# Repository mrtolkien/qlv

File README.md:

# qlv

Quelle Vie (QLV) keyboard

```plaintext
     C0  C1  C2  C3  C4    C4  C3  C2  C1  C0
R0   .   .   .   .   .     .   .   .   .   .   R4
R1   .   .   .   .   .     .   .   .   .   .   R5
R2   .   .   .   .   .     .   .   .   .   .   R6

R3            .  .   .     .   .   .           R7
```

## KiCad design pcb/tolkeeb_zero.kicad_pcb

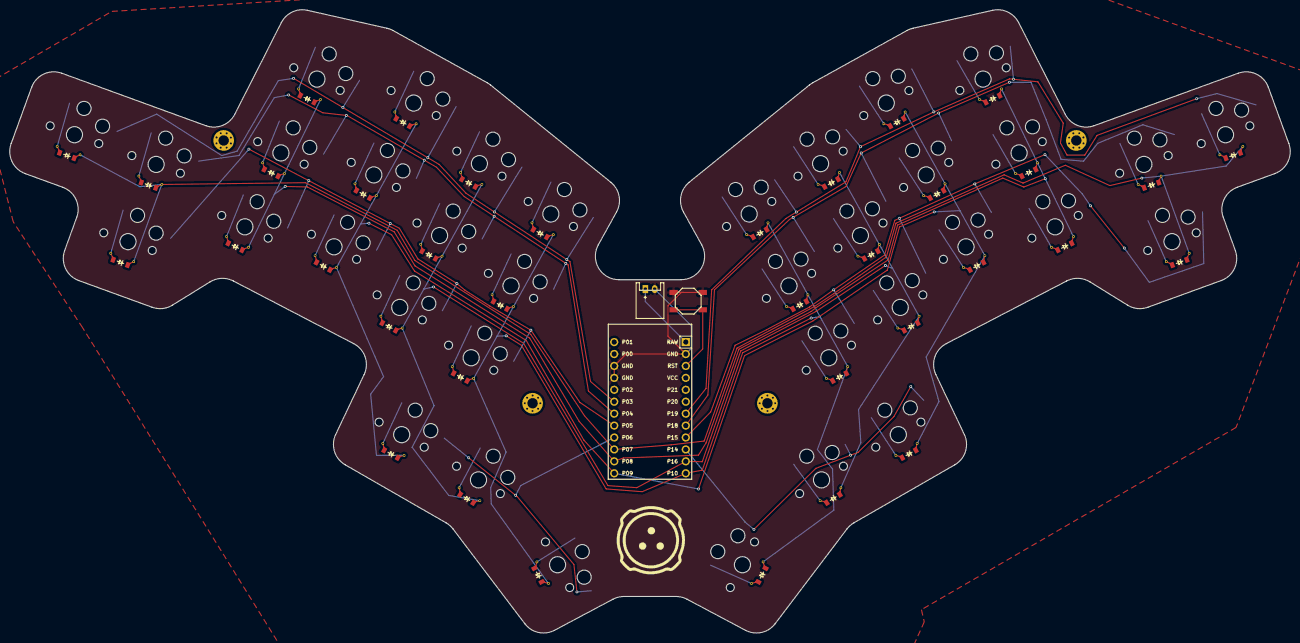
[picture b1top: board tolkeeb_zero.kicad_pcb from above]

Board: 4 copper layers, 272.7 x 132.7 mm, 115 parts (0 on the bottom side), 52 nets.

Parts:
B1: SW_TACT_ALPS_SKQGABE010
D1, D2, D3, D4, D5, D6, D7, D8, D9, D10, D11, D12, D13, D14, D15, D16, D17, D18, D19, D20, D21, D22, D23, D24, D25, D26, D27, D28, D29, D30, D31, D32, D33, D34, D35, D36: ComboDiode
JST1: JST_PH_S2B-PH-K_02x2.00mm_Angled
MCU1: ProMicro
S1, S2, S3, S4, S5, S6, S7, S8, S9, S10, S11, S12, S13, S14, S15, S16, S17, S18, S19, S20, S21, S22, S23, S24, S25, S26, S27, S28, S29, S30, S31, S32, S33, S34, S35, S36: PG1350
SB1, SB2, SB3, SB4, SB5, SB6, SB7, SB8, SB9, SB10, SB11, SB12, SB13, SB14, SB15, SB16, SB17, SB18, SB19, SB20, SB21, SB22, SB23, SB24, SB25, SB26, SB27, SB28, SB29, SB30, SB31, SB32, SB33, SB34, SB35, SB36: ChocBonusGoodies
_1, _2, _3, _4: MountingHole_2.2mm_M2_Pad_Via

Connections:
GND: B1.1, JST1.2, MCU1.2, MCU1.15, MCU1.16
P3: MCU1.18, S1.2, S6.2, S9.2, S12.2, S15.2
P4: MCU1.19, S3.2, S5.2, S8.2, S11.2, S14.2
P5: MCU1.20, S2.2, S4.2, S7.2, S10.2, S13.2
P6: MCU1.21, S31.2, S32.2, S33.2
P7: D1.1, D1.3, D1.4, D2.1, D2.3, D2.4, D3.1, D3.3, D3.4, D16.1, D16.3, D16.4, D17.1, D17.3, D17.4, D18.1, D18.3, D18.4, MCU1.22
P8: D4.1, D4.3, D4.4, D5.1, D5.3, D5.4, D6.1, D6.3, D6.4, D19.1, D19.3, D19.4, D20.1, D20.3, D20.4, D21.1, D21.3, D21.4, MCU1.23
P9: D7.1, D7.3, D7.4, D8.1, D8.3, D8.4, D9.1, D9.3, D9.4, D22.1, D22.3, D22.4, D23.1, D23.3, D23.4, D24.1, D24.3, D24.4, D31.1, D31.3, D31.4, D34.1, D34.3, D34.4, MCU1.24
P10: D13.1, D13.3, D13.4, D14.1, D14.3, D14.4, D15.1, D15.3, D15.4, D28.1, D28.3, D28.4, D29.1, D29.3, D29.4, D30.1, D30.3, D30.4, D33.1, D33.3, D33.4, D36.1, D36.3, D36.4, MCU1.12
P14: MCU1.10, S34.2, S35.2, S36.2
P15: MCU1.9, S17.2, S19.2, S22.2, S25.2, S28.2
P16: D10.1, D10.3, D10.4, D11.1, D11.3, D11.4, D12.1, D12.3, D12.4, D25.1, D25.3, D25.4, D26.1, D26.3, D26.4, D27.1, D27.3, D27.4, D32.1, D32.3, D32.4, D35.1, D35.3, D35.4, MCU1.11
P18: MCU1.8, S18.2, S20.2, S23.2, S26.2, S29.2
P19: MCU1.7, S16.2, S21.2, S24.2, S27.2, S30.2
RAW: JST1.1, MCU1.1
RST: B1.2, MCU1.3
center_default: D32.2, D32.6, D32.7, S32.1
index_bottom: D10.2, D10.6, D10.7, S10.1
index_home: D11.2, D11.6, D11.7, S11.1
index_top: D12.2, D12.6, D12.7, S12.1
inner_bottom: D13.2, D13.6, D13.7, S13.1
inner_default: D31.2, D31.6, D31.7, S31.1
inner_home: D14.2, D14.6, D14.7, S14.1
inner_top: D15.2, D15.6, D15.7, S15.1
middle_bottom: D7.2, D7.6, D7.7, S7.1
middle_home: D8.2, D8.6, D8.7, S8.1
middle_top: D9.2, D9.6, D9.7, S9.1
mirror_center_default: D35.2, D35.6, D35.7, S35.1
mirror_index_bottom: D25.2, D25.6, D25.7, S25.1
mirror_index_home: D26.2, D26.6, D26.7, S26.1
mirror_index_top: D27.2, D27.6, D27.7, S27.1
mirror_inner_bottom: D28.2, D28.6, D28.7, S28.1
mirror_inner_default: D34.2, D34.6, D34.7, S34.1
mirror_inner_home: D29.2, D29.6, D29.7, S29.1
mirror_inner_top: D30.2, D30.6, D30.7, S30.1
mirror_middle_bottom: D22.2, D22.6, D22.7, S22.1
mirror_middle_home: D23.2, D23.6, D23.7, S23.1
mirror_middle_top: D24.2, D24.6, D24.7, S24.1
mirror_outer_default: D36.2, D36.6, D36.7, S36.1
mirror_pinky_bottom: D17.2, D17.6, D17.7, S17.1
mirror_pinky_extension_home: D16.2, D16.6, D16.7, S16.1
mirror_pinky_home: D18.2, D18.6, D18.7, S18.1
mirror_ring_bottom: D19.2, D19.6, D19.7, S19.1
mirror_ring_home: D20.2, D20.6, D20.7, S20.1
mirror_ring_top: D21.2, D21.6, D21.7, S21.1
outer_default: D33.2, D33.6, D33.7, S33.1
pinky_bottom: D2.2, D2.6, D2.7, S2.1
pinky_extension_home: D1.2, D1.6, D1.7, S1.1
pinky_home: D3.2, D3.6, D3.7, S3.1
ring_bottom: D4.2, D4.6, D4.7, S4.1
ring_home: D5.2, D5.6, D5.7, S5.1
ring_top: D6.2, D6.6, D6.7, S6.1

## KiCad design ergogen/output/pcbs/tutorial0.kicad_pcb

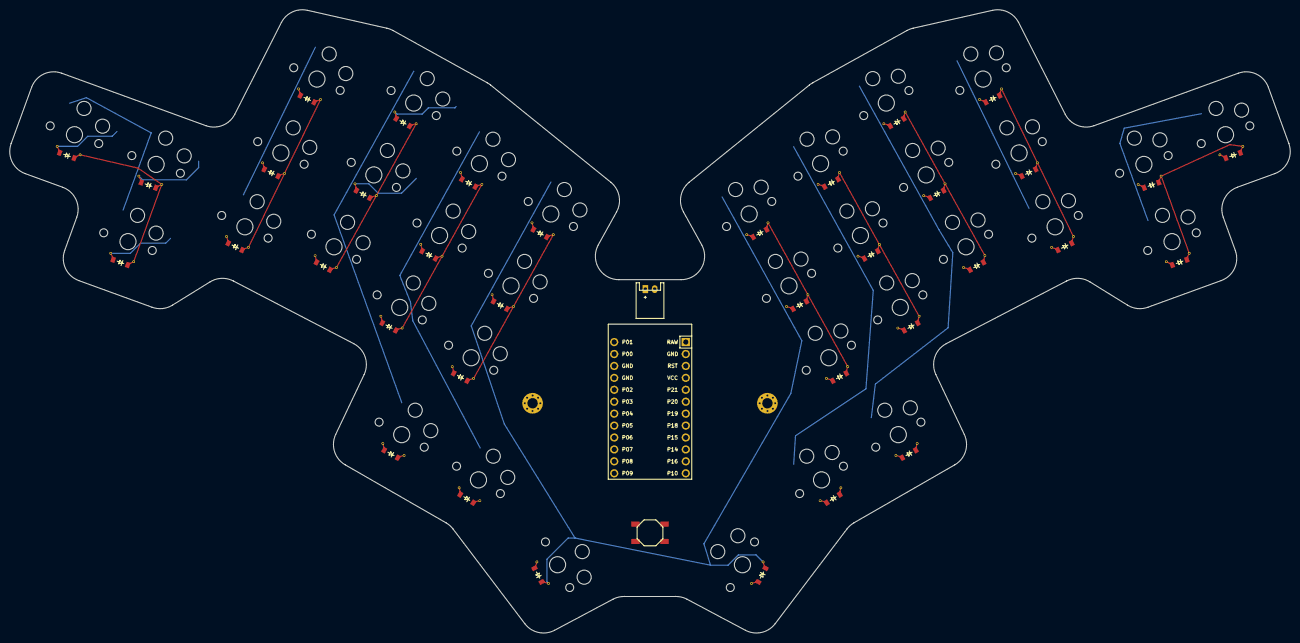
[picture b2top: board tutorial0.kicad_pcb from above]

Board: 2 copper layers, 272.7 x 132.7 mm, 77 parts (0 on the bottom side), 44 nets.

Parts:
B1: SW_TACT_ALPS_SKQGABE010
D1, D2, D3, D4, D5, D6, D7, D8, D9, D10, D11, D12, D13, D14, D15, D16, D17, D18, D19, D20, D21, D22, D23, D24, D25, D26, D27, D28, D29, D30, D31, D32, D33, D34, D35, D36: ComboDiode
JST1: JST_PH_S2B-PH-K_02x2.00mm_Angled
MCU1: ProMicro
S1, S2, S3, S4, S5, S6, S7, S8, S9, S10, S11, S12, S13, S14, S15, S16, S17, S18, S19, S20, S21, S22, S23, S24, S25, S26, S27, S28, S29, S30, S31, S32, S33, S34, S35, S36: PG1350
_1, _2: MountingHole_2.2mm_M2_Pad_Via

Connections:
GND: B1.1, JST1.2, MCU1.2, MCU1.15, MCU1.16
P7: D1.1, D1.3, D1.4, D2.1, D2.3, D2.4, D3.1, D3.3, D3.4, D16.1, D16.3, D16.4, D17.1, D17.3, D17.4, D18.1, D18.3, D18.4, MCU1.22, S1.1, S2.1, S3.1, S16.1, S17.1, S18.1
P8: D4.1, D4.3, D4.4, D5.1, D5.3, D5.4, D6.1, D6.3, D6.4, D19.1, D19.3, D19.4, D20.1, D20.3, D20.4, D21.1, D21.3, D21.4, MCU1.23, S4.1, S5.1, S6.1, S19.1, S20.1, S21.1
P9: D7.1, D7.3, D7.4, D8.1, D8.3, D8.4, D9.1, D9.3, D9.4, D22.1, D22.3, D22.4, D23.1, D23.3, D23.4, D24.1, D24.3, D24.4, D31.1, D31.3, D31.4, D34.1, D34.3, D34.4, MCU1.24, S7.1, S8.1, S9.1, S22.1, S23.1, S24.1, S31.1, S34.1
P10: D13.1, D13.3, D13.4, D14.1, D14.3, D14.4, D15.1, D15.3, D15.4, D28.1, D28.3, D28.4, D29.1, D29.3, D29.4, D30.1, D30.3, D30.4, D33.1, D33.3, D33.4, D36.1, D36.3, D36.4, MCU1.12, S13.1, S14.1, S15.1, S28.1, S29.1, S30.1, S33.1, S36.1
P16: D10.1, D10.3, D10.4, D11.1, D11.3, D11.4, D12.1, D12.3, D12.4, D25.1, D25.3, D25.4, D26.1, D26.3, D26.4, D27.1, D27.3, D27.4, D32.1, D32.3, D32.4, D35.1, D35.3, D35.4, MCU1.11, S10.1, S11.1, S12.1, S25.1, S26.1, S27.1, S32.1, S35.1
RAW: JST1.1, MCU1.1
RST: B1.2, MCU1.3
center_default: D32.2, D32.6, D32.7, S32.2
index_bottom: D10.2, D10.6, D10.7, S10.2
index_home: D11.2, D11.6, D11.7, S11.2
index_top: D12.2, D12.6, D12.7, S12.2
inner_bottom: D13.2, D13.6, D13.7, S13.2
inner_default: D31.2, D31.6, D31.7, S31.2
inner_home: D14.2, D14.6, D14.7, S14.2
inner_top: D15.2, D15.6, D15.7, S15.2
middle_bottom: D7.2, D7.6, D7.7, S7.2
middle_home: D8.2, D8.6, D8.7, S8.2
middle_top: D9.2, D9.6, D9.7, S9.2
mirror_center_default: D35.2, D35.6, D35.7, S35.2
mirror_index_bottom: D25.2, D25.6, D25.7, S25.2
mirror_index_home: D26.2, D26.6, D26.7, S26.2
mirror_index_top: D27.2, D27.6, D27.7, S27.2
mirror_inner_bottom: D28.2, D28.6, D28.7, S28.2
mirror_inner_default: D34.2, D34.6, D34.7, S34.2
mirror_inner_home: D29.2, D29.6, D29.7, S29.2
mirror_inner_top: D30.2, D30.6, D30.7, S30.2
mirror_middle_bottom: D22.2, D22.6, D22.7, S22.2
mirror_middle_home: D23.2, D23.6, D23.7, S23.2
mirror_middle_top: D24.2, D24.6, D24.7, S24.2
mirror_outer_default: D36.2, D36.6, D36.7, S36.2
mirror_pinky_bottom: D17.2, D17.6, D17.7, S17.2
mirror_pinky_extension_home: D16.2, D16.6, D16.7, S16.2
mirror_pinky_home: D18.2, D18.6, D18.7, S18.2
mirror_ring_bottom: D19.2, D19.6, D19.7, S19.2
mirror_ring_home: D20.2, D20.6, D20.7, S20.2
mirror_ring_top: D21.2, D21.6, D21.7, S21.2
outer_default: D33.2, D33.6, D33.7, S33.2
pinky_bottom: D2.2, D2.6, D2.7, S2.2
pinky_extension_home: D1.2, D1.6, D1.7, S1.2
pinky_home: D3.2, D3.6, D3.7, S3.2
ring_bottom: D4.2, D4.6, D4.7, S4.2
ring_home: D5.2, D5.6, D5.7, S5.2
ring_top: D6.2, D6.6, D6.7, S6.2

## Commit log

2024-05-31 feat: add first pass on keyboard with custom outline
2024-05-31 feat: add row and column nets
2024-05-31 fix: make thumbs PCB a bit bigger for simpler routing
2024-05-31 feat: add runonsave configuration for the repo, generating svgs for all outlines
2024-06-06 feat: alpha4, proper scale
2024-06-06 feat: alpha 5, thumb update
2024-06-16 feat: alpha 7, keys position final
2024-06-17 feat: custom footprints for extra swag
2024-06-17 feat: vertical routes wired
2024-06-17 chore: ?
2024-06-17 chore: remove vias
2024-06-17 feat: full routing + silkscreen
2024-06-17 fix: update texts on silkscreens
2024-06-17 chore: minimal fixes based on DRC warnings
2024-06-18 feat: add gerbers export 😳
